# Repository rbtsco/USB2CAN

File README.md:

# USB2CAN
Tiny USB to 8Mbps Flexible-Data CAN (/ AUVCAN) adapter based on the STM32L5 and MCP2562FD

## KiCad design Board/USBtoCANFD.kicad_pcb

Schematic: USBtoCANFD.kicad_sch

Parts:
C1: 1uF; 1005_C; Voltage 10V; Tolerance 10%
C2, C4, C5, C6, C7, C8, C9, C10, C11: 0.1uF; 1005_C; Voltage 10V; Tolerance 10%
C3: 10uF; 1005_C; Voltage 10V; Tolerance 10%
D1, D2: TVS; 1006_C; MPN AR0521P1
D3: USER; Duo_LED_1.6x0.8_Kingbright_APHB1608LZGKSURKC
FB1: FILTER; 1608_C
H1, H2: Mount_Hole_Ungrounded; Plain_Hole_2mm
J1: PLUG; USB_A_PCB_traces_small
J2: CAN; JST_XH_S3B-XH-SM4-TB_1x03_P2.50mm_RightAngle
J3: SWD; 4P_3x1.75_P2.0
J4: HEADER; PinHeader_1x04_P2.54mm_Vertical
JP1: BOOT; SolderJumper-2_P1.3mm_Open_RoundedPad1.0x1.5mm
JP2: RESET; SolderJumper-2_P1.3mm_Open_RoundedPad1.0x1.5mm
R1: 120; 1608_C
R2, R3: 680; 1005_C
R4, R5: 10k; 1005_C
SW1: TERM; SPDT_Slide_HRO_K3-1293S; MPN K3-1293S
U1: LP5907UVX-3.3; TI_DSBGA-4_0.875x0.875mm_Layout2x1x2_P0.35mm; MPN LP5907UVX-3.3
U2: MCP2562FD; DFN-8-1EP_3x3mm_P0.65mm_EP1.55x2.4mm
U3: STM32L552C(C-E)Tx; LQFP-48_7x7mm_P0.5mm

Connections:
+3V3: C2.1, C3.1, C5.1, C6.1, C7.1, C8.1, C9.1, C10.1, R2.1, R4.1, R5.2, U1.A2 (OUT), U2.5 (Vio), U3.1 (VBAT), U3.9 (VDDA/VREF+), U3.24 (VDD), U3.36 (VDD), U3.48 (VDD)
+5V: C1.1, FB1.2, J1.1, J4.1, U1.A1 (IN), U1.B1 (EN)
CAN+: J2.2, R1.2, U2.7 (CANH)
CAN-: J2.3, SW1.3 (C), U2.6 (CANL)
CAN_EN: U2.8 (SHDN), U3.43 (PB7)
CAN_RX: U2.4 (RXD), U3.45 (PB8)
CAN_TX: U2.1 (TXD), U3.46 (PB9)
GND: C1.2, C2.2, C3.2, C4.2, C5.2, C6.2, C7.2, C8.2, C9.2, C10.2, C11.2, D1.1 (A1), D2.1 (A1), J1.4, J2.1, J2.MP (MountPin), J3.4, J4.4, JP1.1, JP2.1, R3.2, SW1.MP, U1.B2 (GND), U2.2 (VSS), U2.9 (PAD), U3.8 (VSSA/VREF-), U3.23 (VSS), U3.35 (VSS), U3.47 (VSS)
unnamed: C4.1, FB1.1, U2.3 (VDD)
unnamed: D3.GK (2), R3.1
unnamed: D3.RA (3), R2.2
unnamed: R1.1, SW1.2 (B)
unnamed: JP1.2, R5.1, U3.44 (PH3-BOOT0)
STATUS_LED: D3.GA (1), D3.RK (4), U3.2 (PC13)
SWD_CLK: J3.1, U3.37 (PA14(JTCK/SWCLK))
SWD_IO: J3.2, U3.34 (PA13(JTMS/SWDIO))
USB_D+: D2.2 (A2), J1.3, J4.3, U3.33 (PA12)
USB_D-: D1.2 (A2), J1.2, J4.2, U3.32 (PA11)
nRST: C11.1, J3.3, JP2.2, R4.2, U3.7 (NRST)

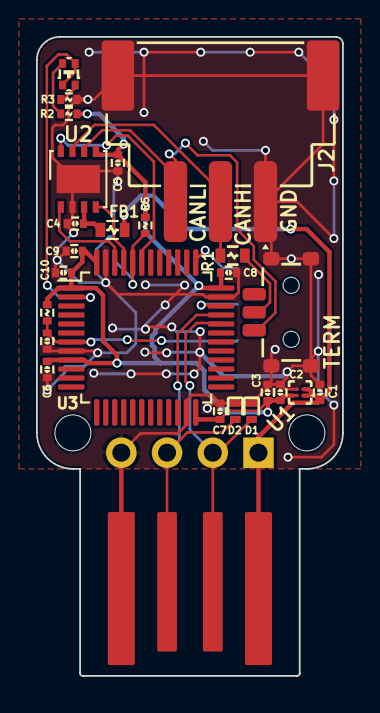
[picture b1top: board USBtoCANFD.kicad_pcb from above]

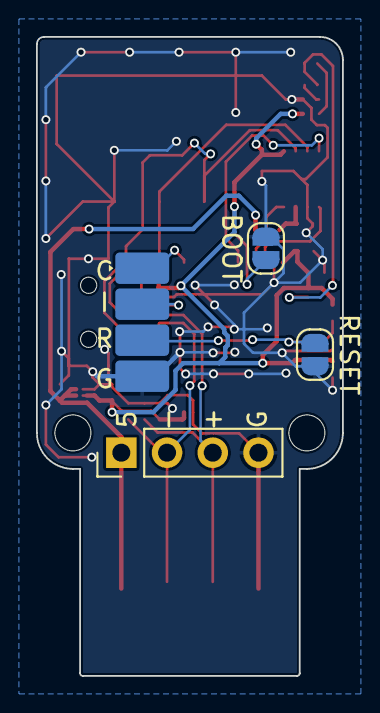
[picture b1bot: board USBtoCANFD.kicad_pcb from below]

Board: 2 copper layers, 17.0 x 35.5 mm, 32 parts (4 on the bottom side), 19 nets.

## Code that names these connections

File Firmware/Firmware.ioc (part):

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Mcu.Name=STM32L552C(C-E)Tx
Mcu.Package=LQFP48
Mcu.UserName=STM32L552CCTx
PA11.Mode=Device
PA11.Signal=USB_DM
PA12.Mode=Device
PA12.Signal=USB_DP
PA13\ (JTMS/SWDIO).Mode=Serial_Wire
PA13\ (JTMS/SWDIO).Signal=DEBUG_JTMS-SWDIO
PA14\ (JTCK/SWCLK).Mode=Serial_Wire
PA14\ (JTCK/SWCLK).Signal=DEBUG_JTCK-SWCLK
PB7.GPIOParameters=GPIO_Label
PB7.GPIO_Label=CAN_EN
PB7.Signal=GPIO_Output
PB8.Mode=FDCAN_Activate
PB8.Signal=FDCAN1_RX
PB9.Mode=FDCAN_Activate
PB9.Signal=FDCAN1_TX
PC13.GPIOParameters=GPIO_Label
PC13.GPIO_Label=STATUS_LED
PC13.Signal=GPIO_Output
RCC.HSE_VALUE=16000000
RCC.SYSCLKFreq_VALUE=110000000
RCC.SYSCLKSource=RCC_SYSCLKSOURCE_PLLCLK
board=custom

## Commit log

2021-01-06 Initial version
2021-01-06 Manually configure clocks to not run into MSI issue
